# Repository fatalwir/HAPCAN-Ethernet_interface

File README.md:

# HAPCAN-Ethernet_interface

## TODO:
 - There is an OpenWRT package to program STM32s directly using the Mediatek SoC GPIO pins. Implement that? [https://hackaday.io/project/166859-prism/log/166980-braaains]
 - Replace the MCP3422 ADC by the MCP3423 because of the I2C address collision with BQ32000.
 - ! Add 12p5 to the RTC crystal (Murata GRM1885C1H120JA01D)
 - Look into replacing the CANable interface by MCP2515?

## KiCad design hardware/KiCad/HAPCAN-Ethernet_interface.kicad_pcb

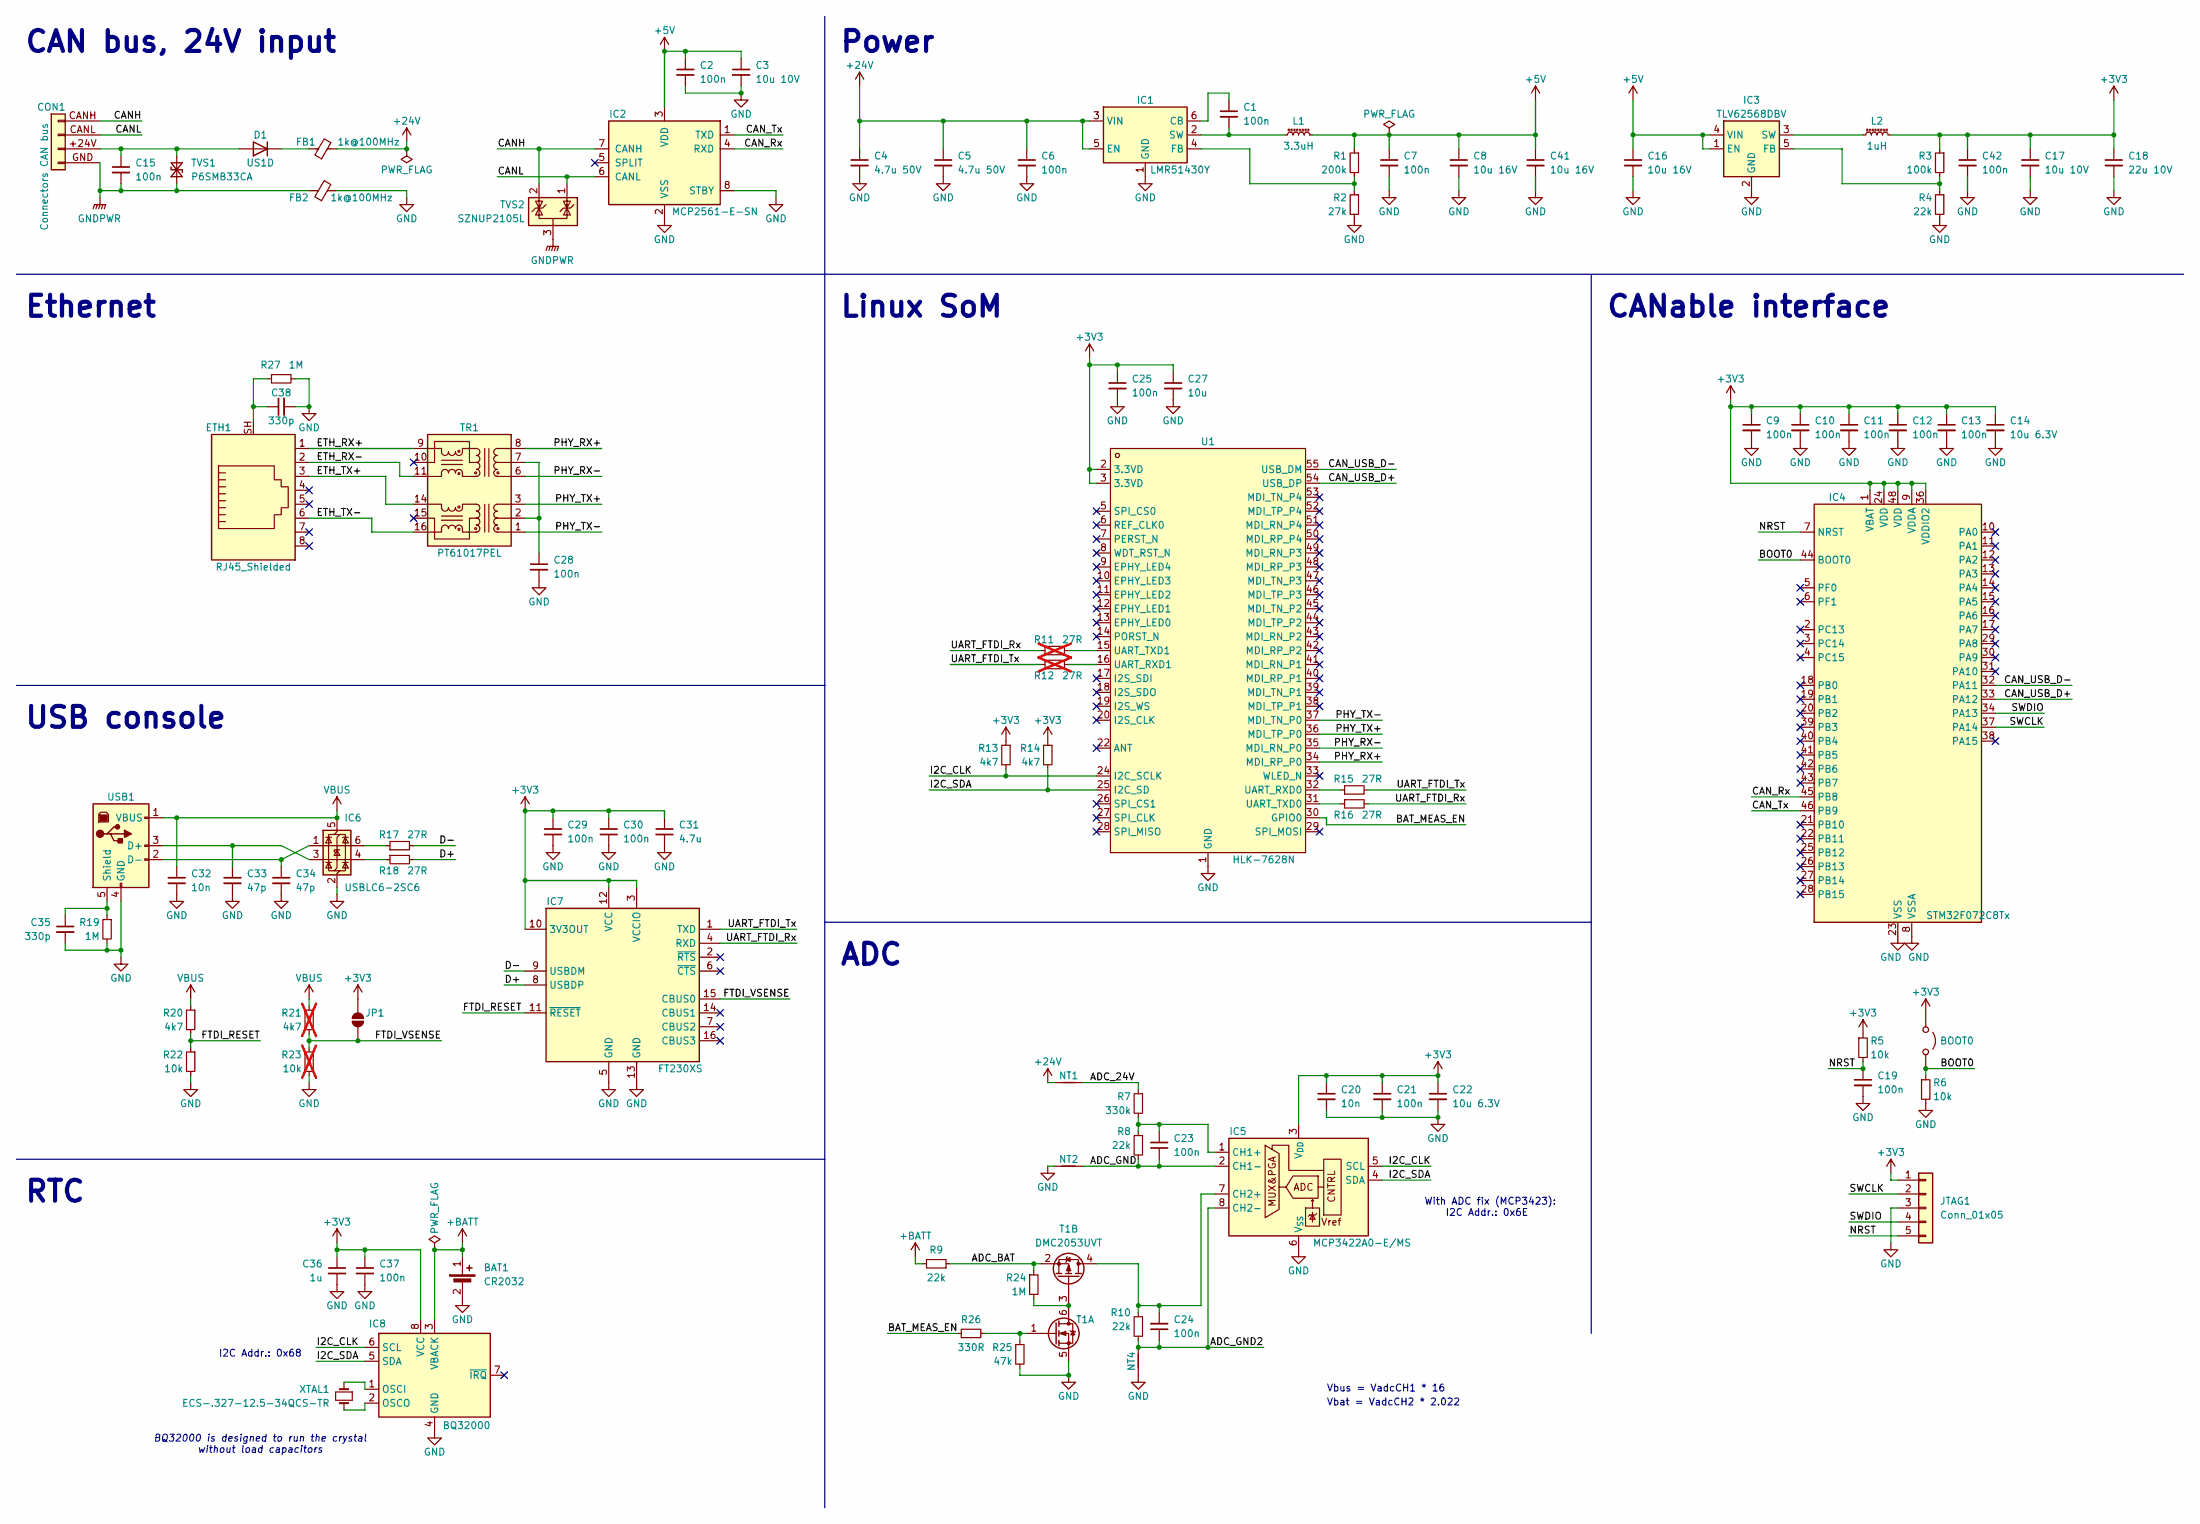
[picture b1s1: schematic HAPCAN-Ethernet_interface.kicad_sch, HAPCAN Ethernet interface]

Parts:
BAT1: CR2032; 1074
BOOT0: Jumper_2_Open; PinHeader_1x02_P2.54mm_Vertical
C1, C2, C6, C7, C9, C10, C11, C12, C13, C15, C19, C21, C23, C24, C25, C28, C29, C30, C37, C42: 100n; C_0603_1608Metric_Pad1.08x0.95mm_HandSolder
C3: 10u 10V; C_1206_3216Metric_Pad1.33x1.80mm_HandSolder
C4, C5: 4.7u 50V; C_1210_3225Metric_Pad1.33x2.70mm_HandSolder
C8, C16, C41: 10u 16V; C_1210_3225Metric_Pad1.33x2.70mm_HandSolder
C14, C22: 10u 6.3V; C_1206_3216Metric_Pad1.33x1.80mm_HandSolder
C17: 10u 10V; C_1210_3225Metric_Pad1.33x2.70mm_HandSolder
C18: 22u 10V; C_1210_3225Metric_Pad1.33x2.70mm_HandSolder
C20, C32: 10n; C_0603_1608Metric_Pad1.08x0.95mm_HandSolder
C27: 10u; C_1206_3216Metric_Pad1.33x1.80mm_HandSolder
C31: 4.7u; C_1206_3216Metric_Pad1.33x1.80mm_HandSolder
C33, C34: 47p; C_0603_1608Metric_Pad1.08x0.95mm_HandSolder
C35, C38: 330p; C_0603_1608Metric_Pad1.08x0.95mm_HandSolder
C36: 1u; C_0805_2012Metric_Pad1.18x1.45mm_HandSolder
CON1: Connectors CAN bus; Conn_CAN-Bus
D1: US1D; D_SMA_Handsoldering
ETH1: RJ45_Shielded; RJ45_Ninigi_GE
FB1, FB2: 1k@100MHz; L_0805_2012Metric_Pad1.15x1.40mm_HandSolder
IC1: LMR51430Y; SOT-23-6
IC2: MCP2561-E-SN; SOIC-8_3.9x4.9mm_P1.27mm
IC3: TLV62568DBV; SOT-23-5
IC4: STM32F072C8Tx; LQFP-48_7x7mm_P0.5mm
IC5: MCP3422A0-E/MS; MSOP-8_3x3mm_P0.65mm
IC6: USBLC6-2SC6; SOT-23-6_Handsoldering
IC7: FT230XS; SSOP-16_3.9x4.9mm_P0.635mm
IC8: BQ32000; SOIC-8_3.9x4.9mm_P1.27mm
JP1: SolderJumper_2_Open; SolderJumper-2_P1.3mm_Open_TrianglePad1.0x1.5mm
JTAG1: Conn_01x05; PinHeader_1x05_P2.54mm_Vertical
L1: 3.3uH; SPM7054VT
L2: 1uH; SPM7054VT
NT1, NT2, NT4: NetTie_2; NetTie-2_SMD_Pad0.5mm
R1: 200k; R_0603_1608Metric_Pad0.98x0.95mm_HandSolder
R2: 27k; R_0603_1608Metric_Pad0.98x0.95mm_HandSolder
R3: 100k; R_0603_1608Metric_Pad0.98x0.95mm_HandSolder
R4, R8, R9, R10: 22k; R_0603_1608Metric_Pad0.98x0.95mm_HandSolder
R5, R6, R22: 10k; R_0603_1608Metric_Pad0.98x0.95mm_HandSolder
R7: 330k; R_0603_1608Metric_Pad0.98x0.95mm_HandSolder
R11, R12: 27R; R_0603_1608Metric_Pad0.98x0.95mm_HandSolder; not fitted
R13, R14, R20: 4k7; R_0603_1608Metric_Pad0.98x0.95mm_HandSolder
R15, R16, R17, R18: 27R; R_0603_1608Metric_Pad0.98x0.95mm_HandSolder
R19, R24, R27: 1M; R_0603_1608Metric_Pad0.98x0.95mm_HandSolder
R21: 4k7; R_0603_1608Metric_Pad0.98x0.95mm_HandSolder; not fitted
R23: 10k; R_0603_1608Metric_Pad0.98x0.95mm_HandSolder; not fitted
R25: 47k; R_0603_1608Metric_Pad0.98x0.95mm_HandSolder
R26: 330R; R_0603_1608Metric_Pad0.98x0.95mm_HandSolder
T1: DMC2053UVT; TSOT-23-6
TR1: PT61017PEL; Transformer_Ethernet_Bourns_PT61017PEL
TVS1: P6SMB33CA; D_SMB_Handsoldering
TVS2: SZNUP2105L; SOT-23-3
U1: HLK-7628N
USB1: https://www.aliexpress.com/item/4000926155068.html; PinHeader_1x05_P2.54mm_Vertical
XTAL1: ECS-.327-12.5-34QCS-TR; Crystal_SMD_EuroQuartz_EQ161-2Pin_3.2x1.5mm_HandSoldering

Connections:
+3V3: BOOT0.1 (A), C9.1, C10.1, C11.1, C12.1, C13.1, C14.1, C17.1, C18.1, C20.1, C21.1, C22.1, C25.1, C27.1, C29.1, C30.1, C31.1, C36.1, C37.1, C42.1, IC4.1 (VBAT), IC4.9 (VDDA), IC4.24 (VDD), IC4.36 (VDDIO2), IC4.48 (VDD), IC5.3 (V_{DD}), IC7.3 (VCCIO), IC7.10 (3V3OUT), IC7.12 (VCC), IC8.8 (VCC), JP1.2 (B), JTAG1.1, L2.2, R3.1, R5.1, R13.1, R14.1, U1.2 (3.3VD), U1.3 (3.3VD)
+5V: C2.1, C3.1, C7.1, C8.1, C16.1, C41.1, IC2.3 (VDD), IC3.1 (EN), IC3.4 (VIN), L1.2, R1.1
+24V: C4.1, C5.1, C6.1, FB1.2, IC1.3 (VIN), IC1.5 (EN), NT1.1
+BATT: BAT1.1 (+), IC8.3 (VBACK), R9.2
/ADC_24V: NT1.2, R7.1
/ADC_BAT: R9.1, R24.1, T1.2 (S)
/ADC_GND: C23.1, IC5.2 (CH1-), NT2.2, R8.2
/ADC_GND2: C24.1, IC5.8 (CH2-), NT4.2, R10.2
/BAT_MEAS_EN: R26.1, U1.30 (GPIO0)
/BOOT0: BOOT0.2 (B), IC4.44 (BOOT0), R6.1
/CANH: CON1.CANH, IC2.7 (CANH), TVS2.2 (K)
/CANL: CON1.CANL, IC2.6 (CANL), TVS2.1 (K)
/CAN_Rx: IC2.4 (RXD), IC4.45 (PB8)
/CAN_Tx: IC2.1 (TXD), IC4.46 (PB9)
/CAN_USB_D+: IC4.33 (PA12), U1.54 (USB_DP)
/CAN_USB_D-: IC4.32 (PA11), U1.55 (USB_DM)
/D+: IC7.8 (USBDP), R18.2
/D-: IC7.9 (USBDM), R17.2
/ETH_RX+: ETH1.1, TR1.9 (RX-)
/ETH_RX-: ETH1.2, TR1.11 (RX+)
/ETH_TX+: ETH1.3, TR1.14 (TX-)
/ETH_TX-: ETH1.6, TR1.16 (TX+)
/FTDI_RESET: IC7.11 (~RESET), R20.2, R22.1
/FTDI_VSENSE: IC7.15 (CBUS0), JP1.1 (A), R21.2, R23.1
/I2C_CLK: IC5.5 (SCL), IC8.6 (SCL), R13.2, U1.24 (I2C_SCLK)
/I2C_SDA: IC5.4 (SDA), IC8.5 (SDA), R14.2, U1.25 (I2C_SD)
/NRST: C19.1, IC4.7 (NRST), JTAG1.5, R5.2
/PHY_RX+: TR1.8 (RD-), U1.34 (MDI_RP_P0)
/PHY_RX-: TR1.6 (RD+), U1.35 (MDI_RN_P0)
/PHY_TX+: TR1.3 (TD-), U1.36 (MDI_TP_P0)
/PHY_TX-: TR1.1 (TD+), U1.37 (MDI_TN_P0)
/SWCLK: IC4.37 (PA14), JTAG1.2
/SWDIO: IC4.34 (PA13), JTAG1.4
/UART_FTDI_Rx: IC7.4 (RXD), R11.1, R16.2
/UART_FTDI_Tx: IC7.1 (TXD), R12.1, R15.2
GND: BAT1.2 (-), C2.2, C3.2, C4.2, C5.2, C6.2, C7.2, C8.2, C9.2, C10.2, C11.2, C12.2, C13.2, C14.2, C16.2, C17.2, C18.2, C19.2, C20.2, C21.2, C22.2, C25.2, C27.2, C28.2, C29.2, C30.2, C31.2, C32.2, C33.2, C34.2, C35.2, C36.2, C37.2, C38.2, C41.2, C42.2, FB2.2, IC1.1 (GND), IC2.2 (VSS), IC2.8 (STBY), IC3.2 (GND), IC4.8 (VSSA), IC4.23 (VSS), IC4.35 (VSS), IC4.47 (VSS), IC5.6 (V_{SS}), IC6.2 (GND), IC7.5 (GND), IC7.13 (GND), IC8.4 (GND), JTAG1.3, NT2.1, NT4.1, R2.2, R4.2, R6.2, R19.2, R22.2, R23.2, R25.2, R27.2, T1.5 (S), U1.1 (GND), U1.4 (GND), U1.21 (GND), U1.23 (GND), U1.56 (GND), USB1.4 (GND)
GNDPWR: C15.2, CON1.GND, FB2.1, TVS1.1 (A1), TVS2.3 (A)
unnamed: C38.1, ETH1.SH, R27.1
unnamed: C15.1, CON1.+24V, D1.2 (A), TVS1.2 (A2)
unnamed: D1.1 (K), FB1.1
unnamed: C1.1, IC1.6 (CB)
unnamed: IC1.4 (FB), R1.2, R2.1
unnamed: C1.2, IC1.2 (SW), L1.1
unnamed: IC3.5 (FB), R3.2, R4.1
unnamed: IC3.3 (SW), L2.1
unnamed: C23.2, IC5.1 (CH1+), R7.2, R8.1
unnamed: C24.2, IC5.7 (CH2+), R10.1, T1.4 (D)
unnamed: IC6.6 (I/O1), R17.1
unnamed: IC6.4 (I/O2), R18.1
unnamed: IC8.1 (OSCI), XTAL1.1
unnamed: IC8.2 (OSCO), XTAL1.2
unnamed: R24.2, T1.3 (G), T1.6 (D)
unnamed: R25.1, R26.2, T1.1 (G)
unnamed: C28.1, TR1.2 (C_TD), TR1.7 (C_RD)
unnamed: R15.1, U1.32 (UART_RXD0)
unnamed: R12.2, U1.16 (UART_RXD1)
unnamed: R16.1, U1.31 (UART_TXD0)
unnamed: R11.2, U1.15 (UART_TXD1)
unnamed: C33.1, IC6.3 (I/O2), USB1.3 (D+)
unnamed: C34.1, IC6.1 (I/O1), USB1.2 (D-)
unnamed: C35.1, R19.1, USB1.5 (Shield)
VBUS: C32.1, IC6.5 (VBUS), R20.1, R21.1, USB1.1 (VBUS)

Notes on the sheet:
Power
With ADC fix (MCP3423): I2C Addr.: 0x6E
BQ32000 is designed to run the crystal without load capacitors
Linux SoM
ADC
CAN bus, 24V input
CANable interface
I2C Addr.: 0x68
Vbus = VadcCH1 * 16
Vbat = VadcCH2 * 2.022
USB console
RTC
Ethernet

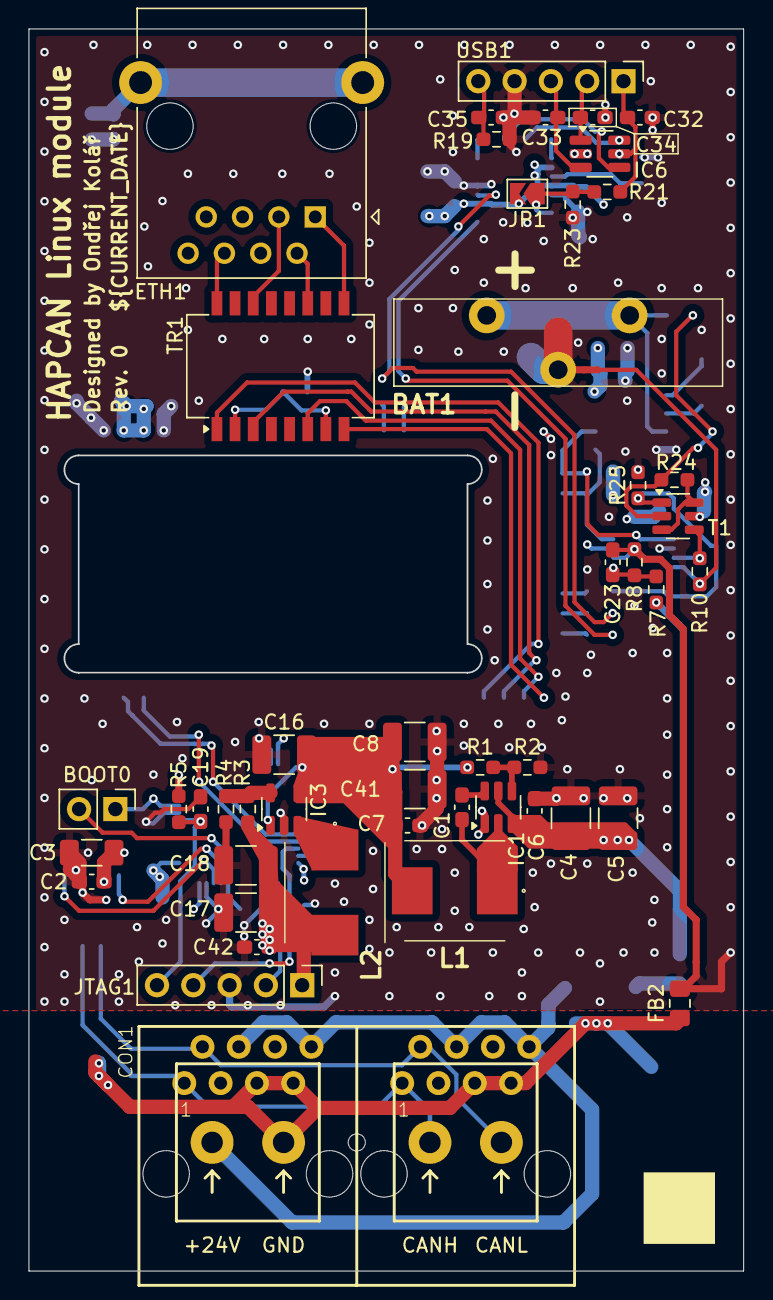
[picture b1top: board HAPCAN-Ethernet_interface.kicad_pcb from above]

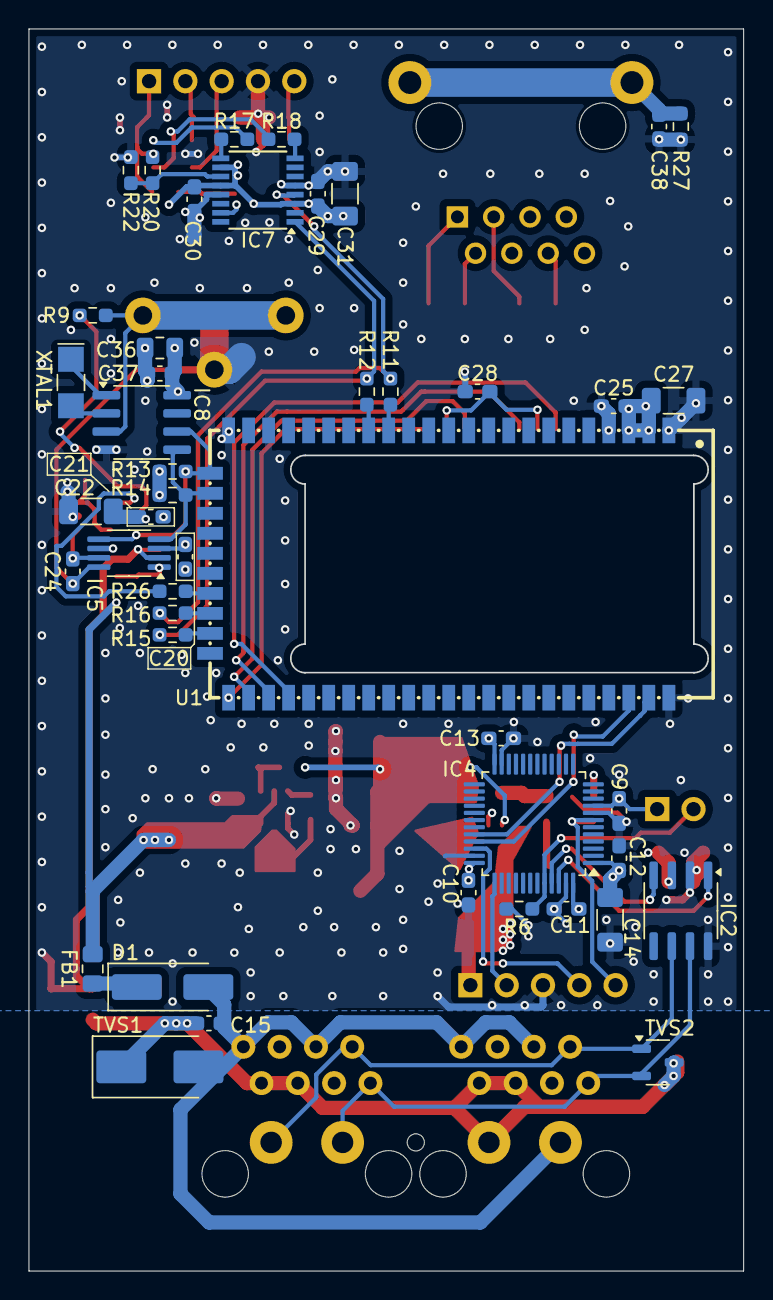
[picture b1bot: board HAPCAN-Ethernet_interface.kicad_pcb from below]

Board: 4 copper layers, 49.9 x 86.8 mm, 95 parts (46 on the bottom side), 62 nets.

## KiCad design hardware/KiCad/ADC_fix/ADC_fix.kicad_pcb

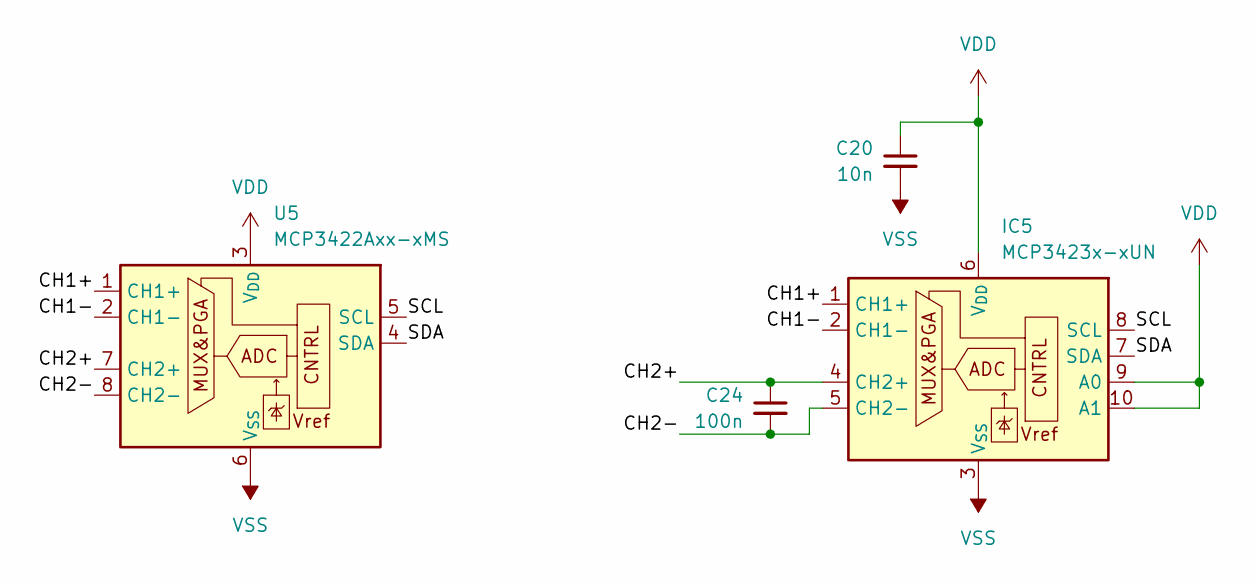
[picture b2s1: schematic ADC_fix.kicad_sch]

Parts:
C20: 10n; C_0603_1608Metric_Pad1.08x0.95mm_HandSolder
C24: 100n; C_0603_1608Metric_Pad1.08x0.95mm_HandSolder
IC5: MCP3423x-xUN; MSOP-10_3x3mm_P0.5mm
U5: MCP3422Axx-xMS; MSOP-8_3x3mm_P0.65mm

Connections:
/CH1+: IC5.1 (CH1+), U5.1 (CH1+)
/CH1-: IC5.2 (CH1-), U5.2 (CH1-)
/CH2+: C24.1, IC5.4 (CH2+), U5.7 (CH2+)
/CH2-: C24.2, IC5.5 (CH2-), U5.8 (CH2-)
/SCL: IC5.8 (SCL), U5.5 (SCL)
/SDA: IC5.7 (SDA), U5.4 (SDA)
VDD: C20.1, IC5.6 (V_{DD}), IC5.9 (A0), IC5.10 (A1), U5.3 (V_{DD})
VSS: C20.2, IC5.3 (V_{SS}), U5.6 (V_{SS})

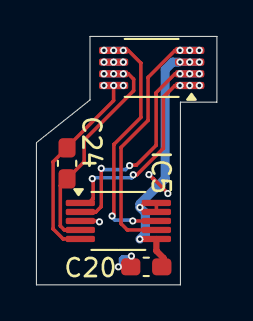
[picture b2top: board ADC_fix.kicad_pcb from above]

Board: 2 copper layers, 10.0 x 13.8 mm, 4 parts (0 on the bottom side), 8 nets.

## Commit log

2024-05-04 Created KiCad project
2024-05-04 Added HLK-7628N symbol and footprint, MODIFICATIONS NOT FINISHED
2024-05-04 Moved KiCad .gitignore to the KiCad project directory
2024-05-06 Added 24V/3V3 step down circuit
2024-05-07 Made some progress in schematic, preliminary component placement on board
2024-05-11 Finished schematic, but needs cleanup. Started component placement on board.
2024-05-25 Did some work on board.
2024-06-23 Added some useful internet links
2024-08-02 Placed almost all footprints on the PCB
2025-04-05 Updated schematic, finished the board routing
2025-04-07 Finished the board (Rev. 0)
2025-05-10 Added TODO list to the README
2025-06-30 Added DNP flag to UART1 resistors (collided connection to UART0)
2025-07-22 Added ADC fix flex PCB project
2025-07-22 Added some TODOs
2025-07-22 Added ADC fix flex PCB design
2025-07-25 Added a task to TODO.
2025-07-25 Added note about crystal load capacitors
2025-08-28 Fixed a resistor value near the ADC, added some notes to the schematic
